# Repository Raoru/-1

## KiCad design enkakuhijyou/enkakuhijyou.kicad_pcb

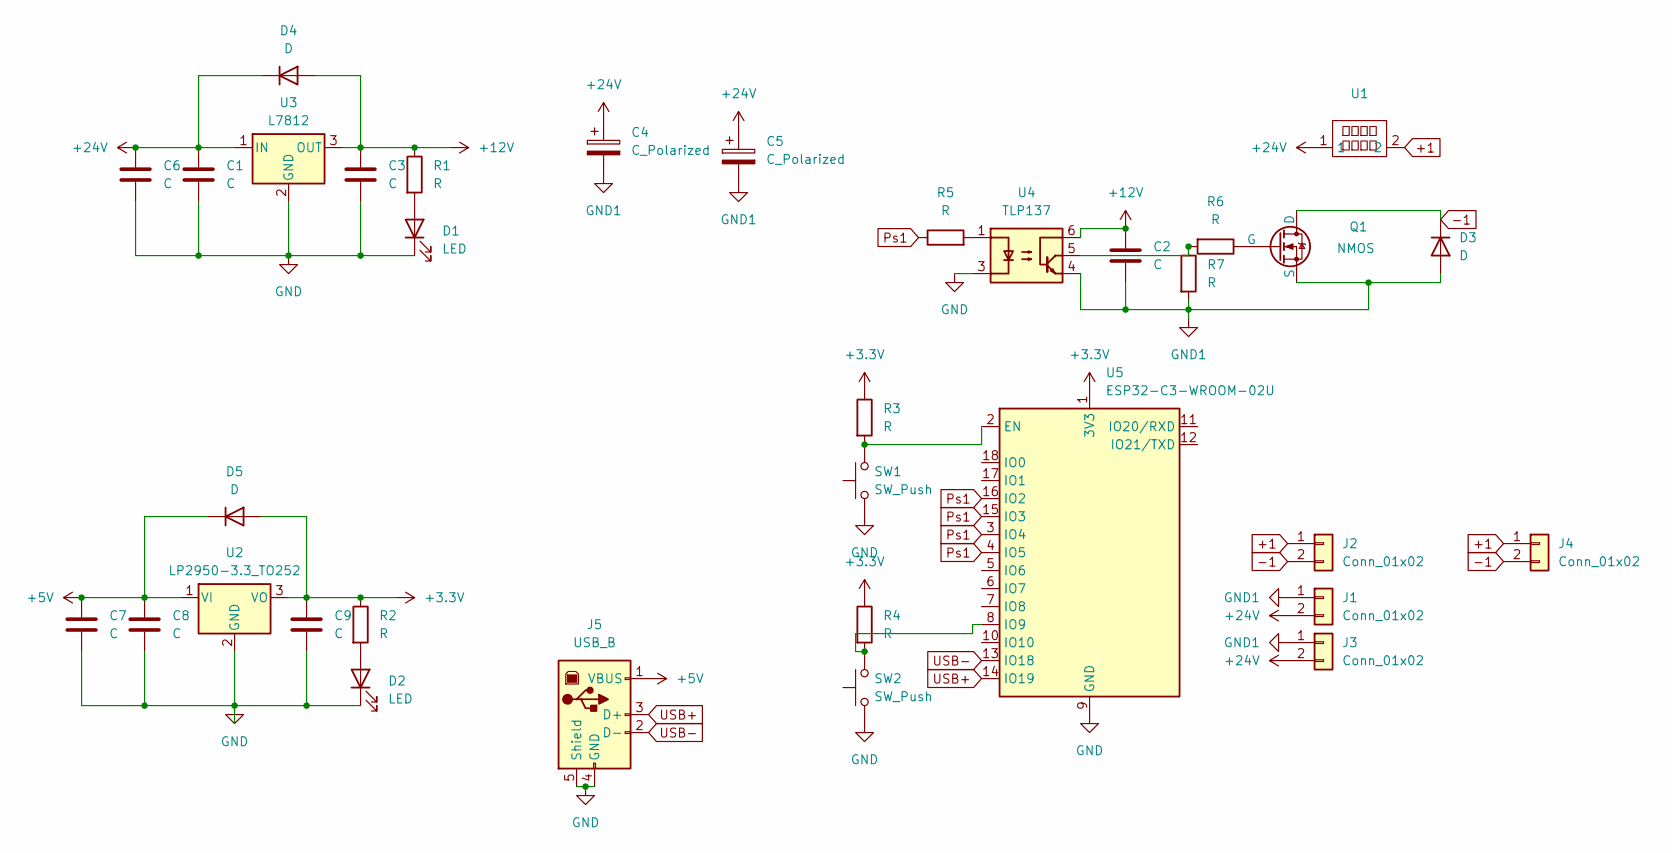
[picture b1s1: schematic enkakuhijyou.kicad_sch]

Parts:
C1, C2, C3, C6, C7, C8, C9: C; C_0603_1608Metric
C4, C5: C_Polarized; CP_Elec_10x10
D1, D2: LED; LED_0603_1608Metric
D3, D4, D5: D; D_SOD-128
J1: Conn_01x02; AMASS_XT60PW-F_1x02_P7.20mm_Horizontal
J2: Conn_01x02; AMASS_XT60PW-M_1x02_P7.20mm_Horizontal
J3, J4: Conn_01x02; AMASS_XT30PW-F_1x02_P2.50mm_Horizontal
J5: USB_B; USB_B_Lumberg_2411_02_Horizontal
Q1: NMOS; TO-263-2
R1, R2, R3, R4, R5, R6, R7: R; R_0603_1608Metric
SW1, SW2: SW_Push; SW_PUSH-12mm
U1: XS-506A
U2: LP2950-3.3_TO252; TO-252-2
U3: L7812; TO-252-2
U4: TLP137; MFSOP6-5_4.4x3.6mm_P1.27mm
U5: ESP32-C3-WROOM-02U

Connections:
+1: J2.1, J4.1, U1.2
+3.3V: C9.1, D5.2 (A), R2.1, R3.1, R4.1, U2.3 (VO), U5.1 (3V3)
+5V: C7.1, C8.1, D5.1 (K), J5.1 (VBUS), U2.1 (VI)
+12V: C2.1, C3.1, D4.2 (A), R1.1, U3.3 (OUT), U4.6
+24V: C1.1, C4.1, C5.1, C6.1, D4.1 (K), J1.2, J3.2, U1.1, U3.1 (IN)
-1: D3.1 (K), J2.2, J4.2, Q1.1 (D)
GND: C1.2, C3.2, C6.2, C7.2, C8.2, C9.2, D1.1 (K), D2.1 (K), J5.4 (GND), J5.5 (Shield), SW1.1, SW2.1, U2.2 (GND), U3.2 (GND), U4.3, U5.9 (GND), U5.19 (GND)
GND1: C2.2, C4.2, C5.2, D3.2 (A), J1.1, J3.1, Q1.3 (S), R7.2, U4.4
unnamed: D1.2 (A), R1.2
unnamed: D2.2 (A), R2.2
unnamed: Q1.2 (G), R6.1
unnamed: R5.2, U4.1
unnamed: R6.2, R7.1, U4.5
unnamed: R3.2, SW1.2, U5.2 (EN)
unnamed: R4.2, SW2.2, U5.8 (IO9)
Ps1: R5.1, U5.3 (IO4), U5.4 (IO5), U5.15 (IO3), U5.16 (IO2)
USB+: J5.3 (D+), U5.14 (IO19)
USB-: J5.2 (D-), U5.13 (IO18)

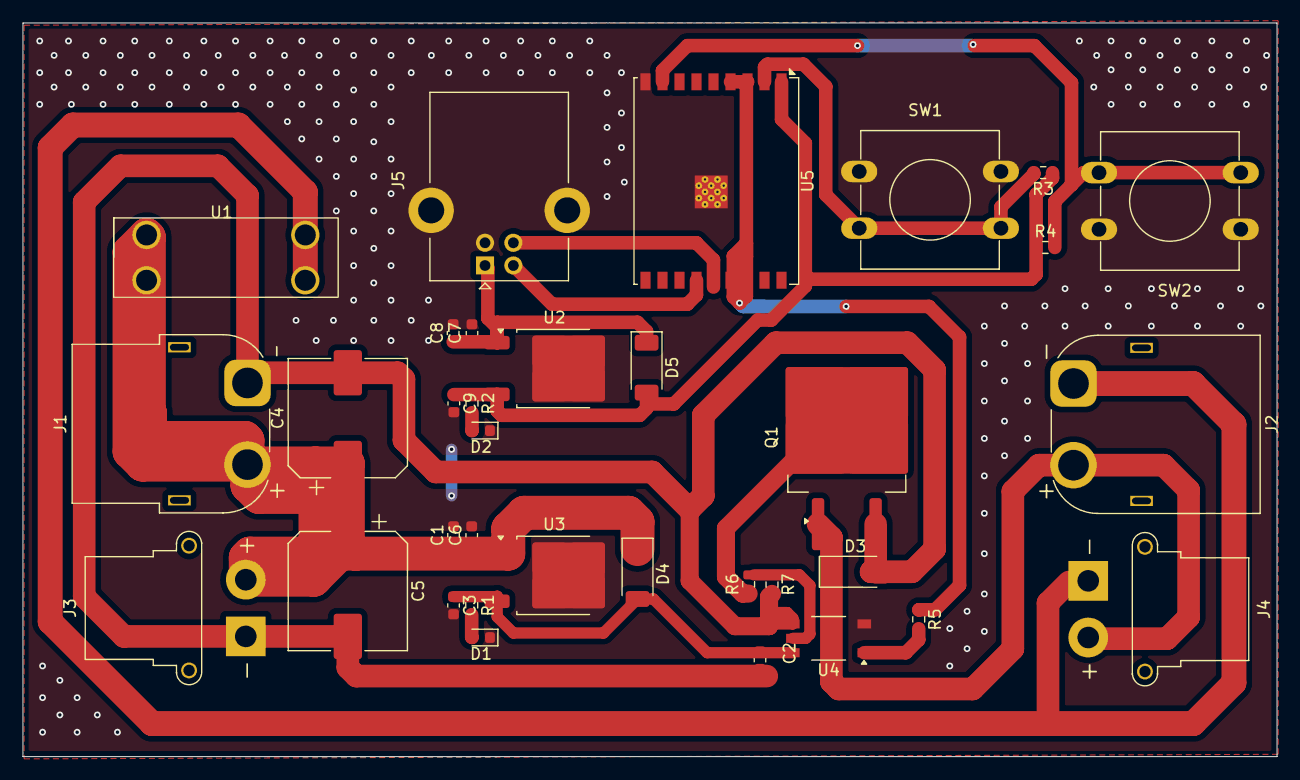
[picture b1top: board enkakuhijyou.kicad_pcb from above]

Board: 2 copper layers, 110.6 x 64.7 mm, 34 parts (0 on the bottom side), 18 nets.
